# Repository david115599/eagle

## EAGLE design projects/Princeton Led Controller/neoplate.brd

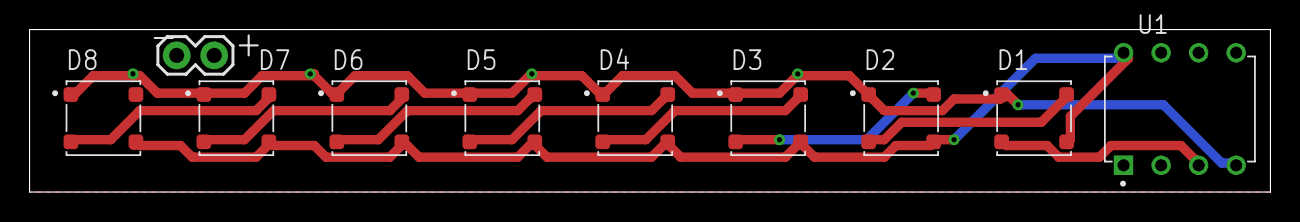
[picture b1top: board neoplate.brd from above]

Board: 2 copper layers, 84.0 x 11.0 mm, 10 parts (0 on the bottom side), 10 nets.

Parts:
D1, D2, D3, D4, D5, D6, D7, D8: 1655; SMD_RGB
JP1: 1X02
U1: ATTINY85-20PU; PDIP-8

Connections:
GND: D1.1, D2.1, D3.1, D4.1, D5.1, D6.1, D7.1, D8.1, JP1.2, U1.4
unnamed: D1.4, D2.2
unnamed: D2.4, D3.2
unnamed: D3.4, D4.2
unnamed: D4.4, D5.2
unnamed: D5.4, D6.2
unnamed: D6.4, D7.2
unnamed: D7.4, D8.2
NEOIN: D1.2, U1.3
VCC: D1.3, D2.3, D3.3, D4.3, D5.3, D6.3, D7.3, D8.3, JP1.1, U1.8

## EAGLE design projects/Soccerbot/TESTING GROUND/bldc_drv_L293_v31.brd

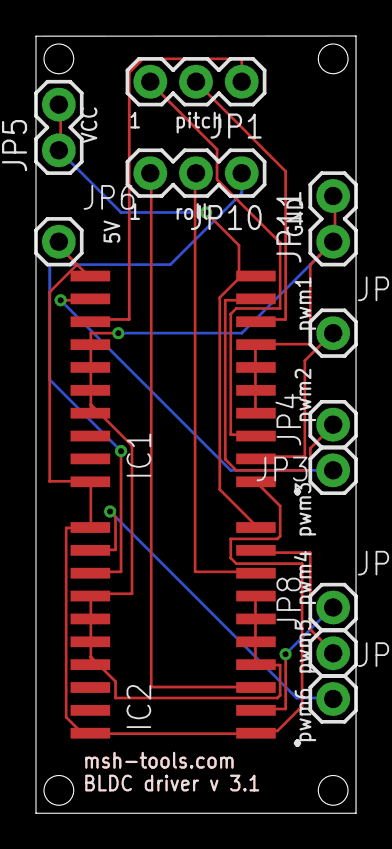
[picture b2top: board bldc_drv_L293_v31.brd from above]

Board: 2 copper layers, 17.8 x 43.2 mm, 13 parts (0 on the bottom side), 15 nets.

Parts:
IC1, IC2: L293DD; SO20
JP1, JP10: 1X03
JP2, JP3, JP4, JP6, JP7, JP8, JP9: M01PTH; 1X01
JP5, JP11: 1X02

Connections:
5V: IC1.1, IC1.11, IC1.20, IC2.1, IC2.11, IC2.20, JP6.1
GND: IC1.4, IC1.5, IC1.6, IC1.7, IC1.14, IC1.15, IC1.16, IC1.17, IC2.4, IC2.5, IC2.6, IC2.7, IC2.14, IC2.15, IC2.16, IC2.17, JP11.1, JP11.2
unnamed: IC2.3, JP10.3
unnamed: IC1.3, JP1.3
unnamed: IC1.8, JP1.2
unnamed: IC1.13, JP1.1
unnamed: IC2.8, JP10.2
unnamed: IC2.13, JP10.1
PWM1: IC1.2, JP2.1
PWM2: IC1.9, JP3.1
PWM3: IC1.12, JP4.1
PWM4: IC2.2, JP7.1
PWM5: IC2.9, JP8.1
PWM6: IC2.12, JP9.1
VCC: IC1.10, IC2.10, JP5.1, JP5.2

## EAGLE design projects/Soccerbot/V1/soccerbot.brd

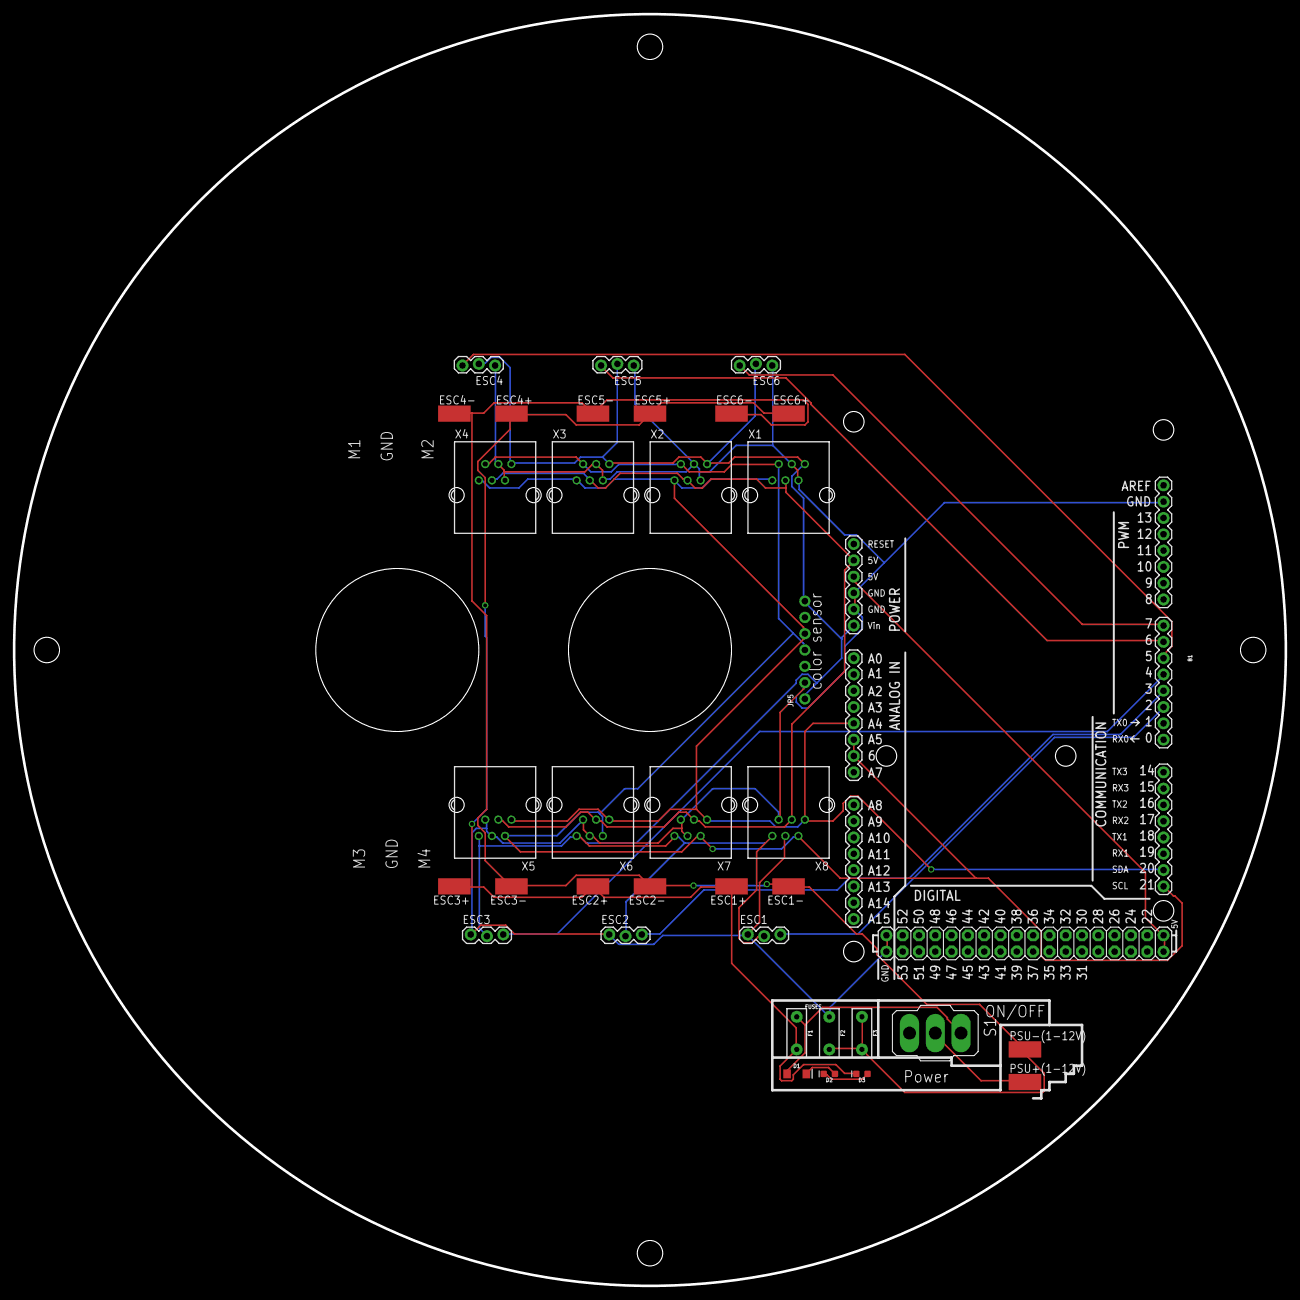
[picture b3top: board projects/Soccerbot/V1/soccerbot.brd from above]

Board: 2 copper layers, 198.1 x 198.1 mm, 37 parts (0 on the bottom side), 18 nets.

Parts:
B1: ARDUINO_MEGA_R3FULL; ARDUINO_MEGA
D1: BLUE; LED-1206
D2: GREEN; LED-0603
D3: RED; LED-0603
ESC1, ESC2, ESC3, ESC4, ESC5, ESC6: 1X03_LOCK
ESC1+, ESC1-, ESC2+, ESC2-, ESC3+, ESC3-, ESC4+, ESC4-, ESC5+, ESC5-, ESC6+, ESC6-: SMD2,54-5,08
F1, F2, F3: 72V/0.25A; PTH
JP5: 1X07_ROUND_70
PSU+(1-12V): SMD2,54-5,08
PSU-(1-12V): SMD2,54-5,08
S1: 320-916
X1, X2, X3, X4, X5, X6, X7, X8: NXT-SOCKET

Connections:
3.3V: B1.3.3V, X1.4, X2.4, X3.4, X4.4, X5.4, X6.4, X7.4, X8.4
5.5V: B1.5V@0, B1.5V@1, B1.5V@2
BAT+: D3.C, ESC1+.1, ESC2+.1, ESC3+.1, ESC4+.1, ESC5+.1, ESC6+.1, F1.P$2
BAT-: ESC1-.1, ESC2-.1, ESC3-.1, ESC4-.1, ESC5-.1, ESC6-.1, F2.P$2, F3.P$1, F3.P$2, PSU-(1-12V).1
D2: B1.2, ESC1.3
D3: B1.3, ESC2.3
D4: B1.4, ESC3.3
D5: B1.5, ESC4.3
D6: B1.6, ESC5.3
D7: B1.7, ESC6.3
GND: B1.GND@0, B1.GND@1, B1.GND@2, B1.GND@3, B1.GND@4, ESC1.1, ESC2.1, ESC3.1, ESC4.1, ESC5.1, ESC6.1, F2.P$1, JP5.2, X1.2, X1.3, X2.2, X2.3, X3.2, X3.3, X4.2, X4.3, X5.2, X5.3, X6.2, X6.3, X7.2, X7.3, X8.2, X8.3
unnamed: D1.C, D2.A
unnamed: PSU+(1-12V).1, S1.2
unnamed: D2.C, D3.A
unnamed: D1.A, F1.P$1, S1.1
SCL: B1.21, B1.A5, JP5.4, X1.5, X2.5, X3.5, X4.5, X5.5, X6.5, X7.5, X8.5
SDA: B1.20, B1.A4, JP5.5, X1.6, X2.6, X3.6, X4.6, X5.6, X6.6, X7.6, X8.6
VIN: B1.VIN, ESC1.2, ESC2.2, ESC3.2, ESC4.2, ESC5.2, ESC6.2, JP5.1, JP5.7, X1.1, X2.1, X3.1, X4.1, X5.1, X6.1, X7.1, X8.1

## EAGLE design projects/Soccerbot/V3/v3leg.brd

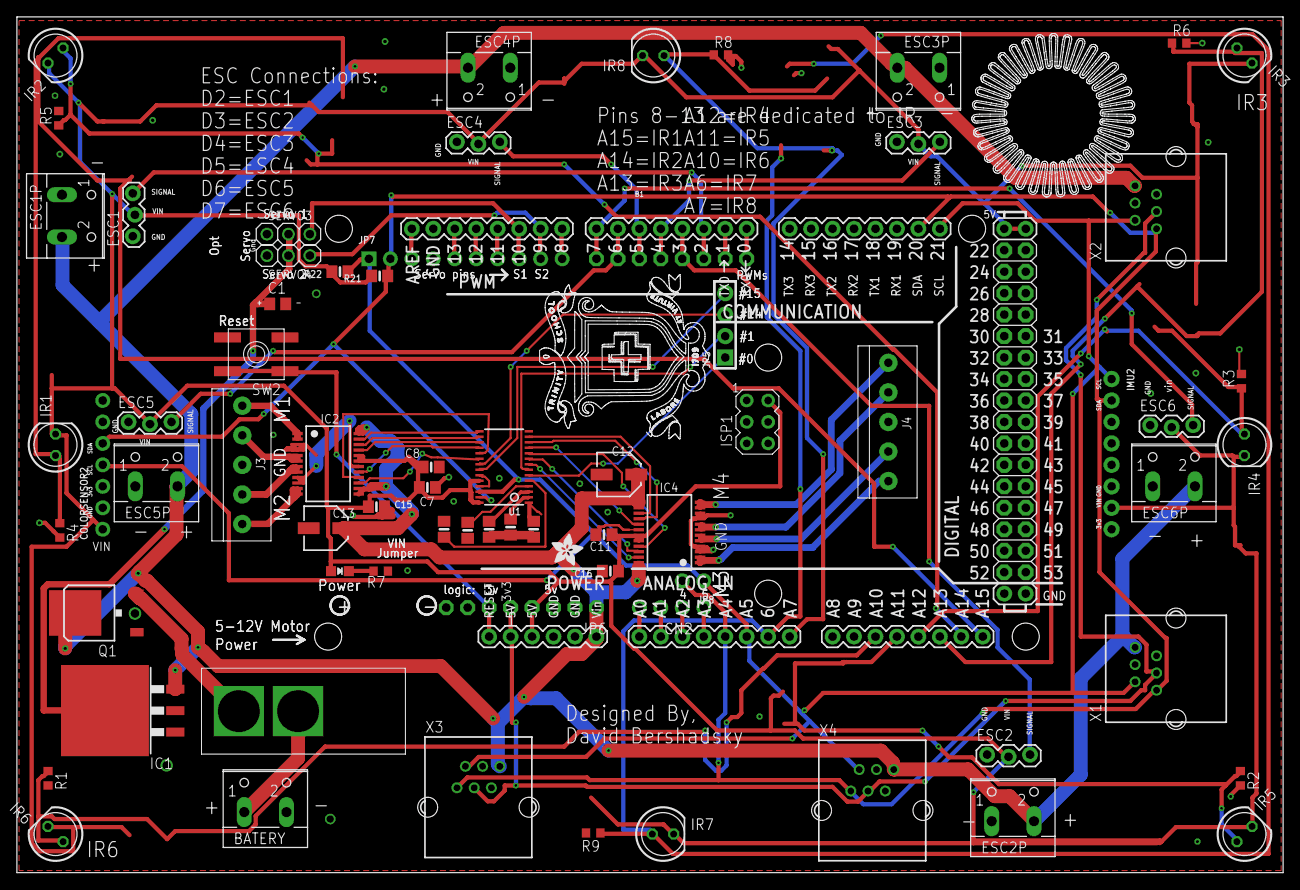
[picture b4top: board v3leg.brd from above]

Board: 2 copper layers, 149.8 x 101.3 mm, 73 parts (1 on the bottom side), 67 nets.

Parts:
B1: ARDUINO_MEGA_R3FULL; ARDUINO_MEGA
BATERY: W237-102
C1: C0805
C7, C8, C11: 0.1uF; 0805-NO
C12: 47uF/16v; PANASONIC_C
C13: 47uF+/16v; PANASONIC_C
C15, C16: 10uF; 0805-NO
CN2: 1X4-CLEANBIG; 1X04-CLEANBIG
COLORSENSOR2: 1X07_ROUND_70
D0-1: 1X08-CLEANBIG
ESC1, ESC2, ESC3, ESC4, ESC5, ESC6: 1X03_LOCK
ESC1P, ESC2P, ESC3P, ESC4P, ESC5P, ESC6P: W237-102
IC1: LM340S-05; TO263-3
IC2, IC4: TB6612FNG; SSOP24
IMU2: 1X08_ROUND_76
IR1, IR2, IR3, IR4, IR5, IR6, IR7, IR8: LED5MM
ISP1: AVRISP-6; AVRISP
J3, J4: 1X5; 1X05-3.5MM
JP5: 1X04_ROUND_76
JP6: 1X08-CLEANBIG
JP7: 1X10_ROUND70
JP8: 1X02_ROUND
LED2: Green; CHIPLED_0805_NOOUTLINE
Q1: AOD417; D-PAK_TO252AA
R1, R2, R3, R4, R5, R6, R8, R9: 49.9k; R0603
R7: 150ohm; R0603
R15, R16, R17, R19, R20: 10k; 0805-NO
R21, R22: 10K; 0805-NO
SERVO3, SERVO4: 1X03
SW2: SPST_TACT-EVQQ2; EVQ-Q2
U1: PCA9685; TSSOP28
U$2: TOGGLESWITCH
U$17: ADAFRUIT_TEXT_30MM
U$18: ADAFRUIT_3.5MM
X1, X2, X3, X4: NXT-SOCKET

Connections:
3.3V: B1.3.3V, JP6.5, X1.4, X2.4, X3.4, X4.4
5.5V: B1.5V@0, B1.5V@1, B1.5V@2, C7.1, C8.1, C11.1, C15.1, C16.1, COLORSENSOR2.1, ESC1.2, ESC2.2, ESC3.2, ESC4.2, ESC5.2, ESC6.2, IC2.19, IC2.20, IC4.19, IC4.20, IMU2.7, IR1.K, IR2.K, IR3.K, IR4.K, IR5.K, IR6.K, IR7.K, IR8.K, ISP1.2, JP6.4, LED2.A, R21.2, R22.2, U1.24, U1.28
A0: R15.2, U1.1
A0A: B1.A0, CN2.4
A1: R16.2, U1.2
A1A: B1.A1, CN2.3
A2: R17.2, U1.3
A2A: B1.A2, CN2.2
A3: R19.2, U1.4
A3A: B1.A3, CN2.1
A4: R20.2, U1.5
A6: B1.A6, IR7.A, R9.1
A7: B1.A7, IR8.A, R8.1
A10: B1.A10, IR6.A, R1.1
A11: B1.A11, IR5.A, R2.1
A12: B1.A12, IR4.A, R3.1
A13: B1.A13, IR3.A, R6.1
A14: B1.A14, IR2.A, R5.1
A15: B1.A15, IR1.A, R4.1
AREF: B1.AREF, JP7.3
BAT+: B1.VIN, C12.+, C13.+, ESC1P.2, ESC2P.2, ESC3P.2, ESC4P.2, ESC5P.2, ESC6P.2, IC1.3, IC2.13, IC2.14, IC2.24, IC4.13, IC4.14, IC4.24, JP6.1, Q1.4, X1.1, X2.1, X3.1, X4.1
D0: B1.0, D0-1.1
D1: B1.1, D0-1.2
D2: B1.2, D0-1.3, ESC1.3
D3: B1.3, D0-1.4, ESC2.3
D4: B1.4, D0-1.5, ESC3.3
D5: B1.5, D0-1.6, ESC4.3
D6: B1.6, D0-1.7, ESC5.3
D7: B1.7, D0-1.8, ESC6.3
D8: B1.8, JP7.10
D9: B1.9, JP7.9, SERVO4.3
D10: B1.10, JP7.8, SERVO3.3
D11: B1.11, JP7.7
D12: B1.12, JP7.6
D13: B1.13, JP7.5
GND: B1.GND@0, B1.GND@1, B1.GND@2, B1.GND@3, B1.GND@4, BATERY.2, C1.2, C7.2, C8.2, C11.2, C12.-, C13.-, C15.2, C16.2, COLORSENSOR2.2, ESC1.1, ESC1P.1, ESC2.1, ESC2P.1, ESC3.1, ESC3P.1, ESC4.1, ESC4P.1, ESC5.1, ESC5P.1, ESC6.1, ESC6P.1, IC1.1, IC2.3, IC2.4, IC2.9, IC2.10, IC2.18, IC4.3, IC4.4, IC4.9, IC4.10, IC4.18, IMU2.6, ISP1.6, J3.3, J4.3, JP6.2, JP6.3, JP7.4, Q1.1, R1.2, R2.2, R3.2, R4.2, R5.2, R6.2, R7.1, R8.2, R9.2, R15.1, R16.1, R17.1, R19.1, R20.1, SERVO3.1, SERVO4.1, SW2.A, SW2.A', U1.14, U1.23, U1.25, X1.2, X1.3, X2.2, X2.3, X3.2, X3.3, X4.2, X4.3
M1A1: IC2.1, IC2.2, J3.5
M1B1: IC2.5, IC2.6, J3.4
M2A1: IC2.11, IC2.12, J3.1
M2B1: IC2.7, IC2.8, J3.2
M3A1: IC4.1, IC4.2, J4.1
M3B1: IC4.5, IC4.6, J4.2
M4A1: IC4.11, IC4.12, J4.5
M4B1: IC4.7, IC4.8, J4.4
unnamed: LED2.C, R7.2
unnamed: BATERY.1, U$2.IN
unnamed: Q1.3, U$2.OUT
PWM0: JP5.1, U1.6
PWM1: JP5.2, U1.7
PWM2: IC4.23, U1.8
PWM3: IC4.22, U1.9
PWM4: IC4.21, U1.10
PWM5: IC4.17, U1.11
PWM6: IC4.16, U1.12
PWM7: IC4.15, U1.13
PWM8: IC2.23, U1.15
PWM9: IC2.22, U1.16
PWM10: IC2.21, U1.17
PWM11: IC2.17, U1.18
PWM12: IC2.16, U1.19
PWM13: IC2.15, U1.20
PWM14: JP5.3, U1.21
PWM15: JP5.4, U1.22
RESET: B1.RESET, JP6.6, SW2.B, SW2.B'
SCL: B1.21, B1.A5, COLORSENSOR2.4, IMU2.1, JP7.1, JP8.1, R22.1, U1.26, X1.5, X2.5, X3.5, X4.5
SDA: B1.20, B1.A4, COLORSENSOR2.5, IMU2.2, JP7.2, JP8.2, R21.1, U1.27, X1.6, X2.6, X3.6, X4.6
SERVO5V: C1.1, IC1.TAB, SERVO3.2, SERVO4.2

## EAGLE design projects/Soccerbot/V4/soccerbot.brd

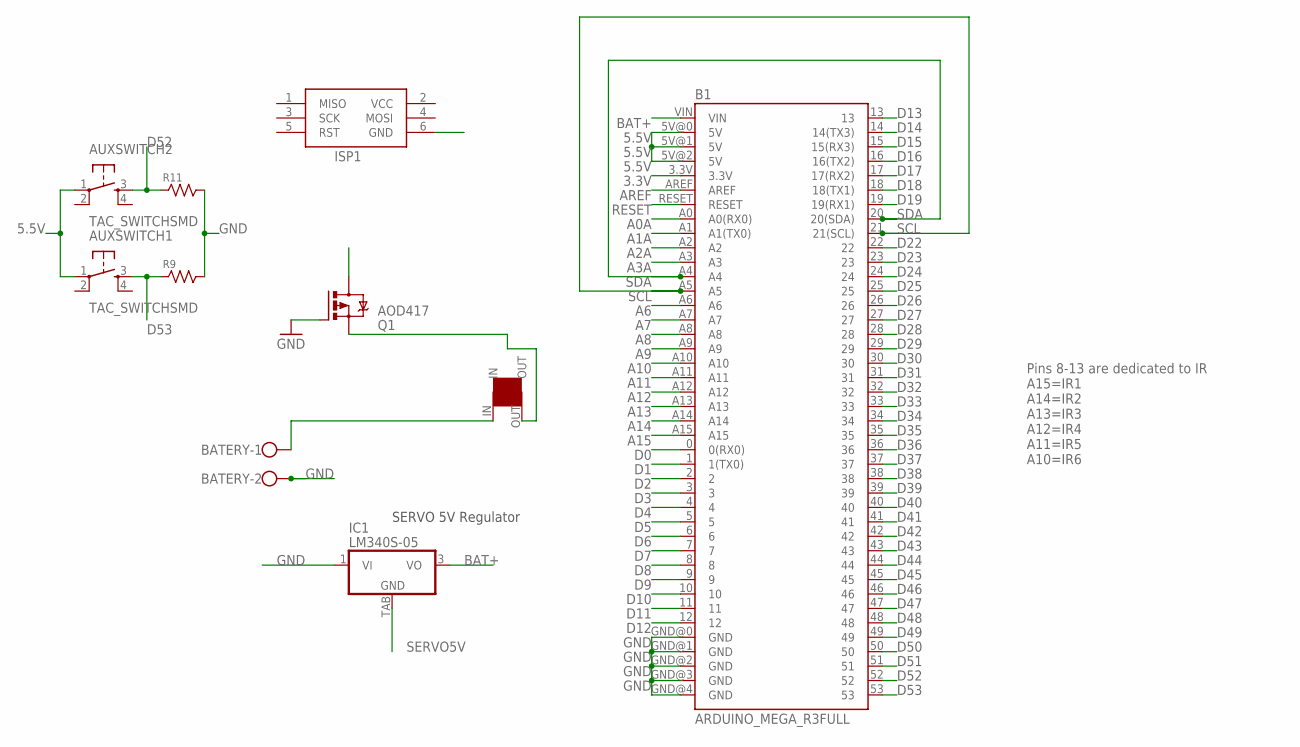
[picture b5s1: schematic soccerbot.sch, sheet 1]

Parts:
AUXSWITCH1, AUXSWITCH2: TAC_SWITCHSMD; TACTILE-SWITCH-SMD
B1: ARDUINO_MEGA_R3FULL; ARDUINO_MEGA
BATERY: W237-102; MPN MA522-500M02
IC1: LM340S-05; TO263-3; MPN LM1085ISX-5.0/NOPB
ISP1: AVRISP-6; AVRISP
Q1: AOD417; D-PAK_TO252AA; MPN AUIRFR540ZTRL
R9, R11: RESISTOR-0603; 0603
U$2: TOGGLESWITCH

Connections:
3.3V: B1.3.3V; also elsewhere on the board
5.5V: AUXSWITCH1.1, AUXSWITCH2.1, B1.5V@0 (5V), B1.5V@1 (5V), B1.5V@2 (5V), ISP1.2 (VCC); also elsewhere on the board
A0A: B1.A0 (A0(RX0))
A1A: B1.A1 (A1(TX0))
A2A: B1.A2
A3A: B1.A3
A6: B1.A6; also elsewhere on the board
A7: B1.A7
A8: B1.A8; also elsewhere on the board
A9: B1.A9
A10: B1.A10; also elsewhere on the board
A11: B1.A11; also elsewhere on the board
A12: B1.A12; also elsewhere on the board
A13: B1.A13; also elsewhere on the board
A14: B1.A14; also elsewhere on the board
A15: B1.A15; also elsewhere on the board
AREF: B1.AREF
BAT+: B1.VIN, IC1.3 (VO), Q1.4 (D); also elsewhere on the board
D0: B1.0 (0(RX0))
D1: B1.1 (1(TX0))
D2: B1.2; also elsewhere on the board
D3: B1.3; also elsewhere on the board
D4: B1.4; also elsewhere on the board
D5: B1.5; also elsewhere on the board
D6: B1.6; also elsewhere on the board
D7: B1.7; also elsewhere on the board
D8: B1.8
D9: B1.9
D10: B1.10
D11: B1.11
D12: B1.12
D13: B1.13
D14: B1.14 (14(TX3))
D15: B1.15 (15(RX3))
D16: B1.16 (16(TX2))
D17: B1.17 (17(RX2))
D18: B1.18 (18(TX1))
D19: B1.19 (19(RX1))
D22: B1.22
D23: B1.23
D24: B1.24
D25: B1.25
D26: B1.26
D27: B1.27
D28: B1.28
D29: B1.29
D30: B1.30
D31: B1.31
D32: B1.32
D33: B1.33
D34: B1.34
D35: B1.35
D36: B1.36
D37: B1.37
D38: B1.38
D39: B1.39
D40: B1.40
D41: B1.41
D42: B1.42
D43: B1.43
D44: B1.44
D45: B1.45
D46: B1.46
D47: B1.47
D48: B1.48
D49: B1.49
D50: B1.50
D51: B1.51
D52: AUXSWITCH2.3, B1.52, R11.1
D53: AUXSWITCH1.3, B1.53, R9.1
GND: B1.GND@0 (GND), B1.GND@1 (GND), B1.GND@2 (GND), B1.GND@3 (GND), B1.GND@4 (GND), BATERY.2, IC1.1 (VI), ISP1.6 (GND), Q1.1 (G), R9.2, R11.2; also elsewhere on the board
unnamed: BATERY.1, U$2.IN
unnamed: Q1.3 (S), U$2.OUT
RESET: B1.RESET
SCL: B1.21 (21(SCL)), B1.A5; also elsewhere on the board
SDA: B1.20 (20(SDA)), B1.A4; also elsewhere on the board
SERVO5V: IC1.TAB (GND)

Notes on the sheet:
Pins 8-13 are dedicated to IR A15=IR1 A14=IR2 A13=IR3 A12=IR4 A11=IR5 A10=IR6
SERVO 5V Regulator

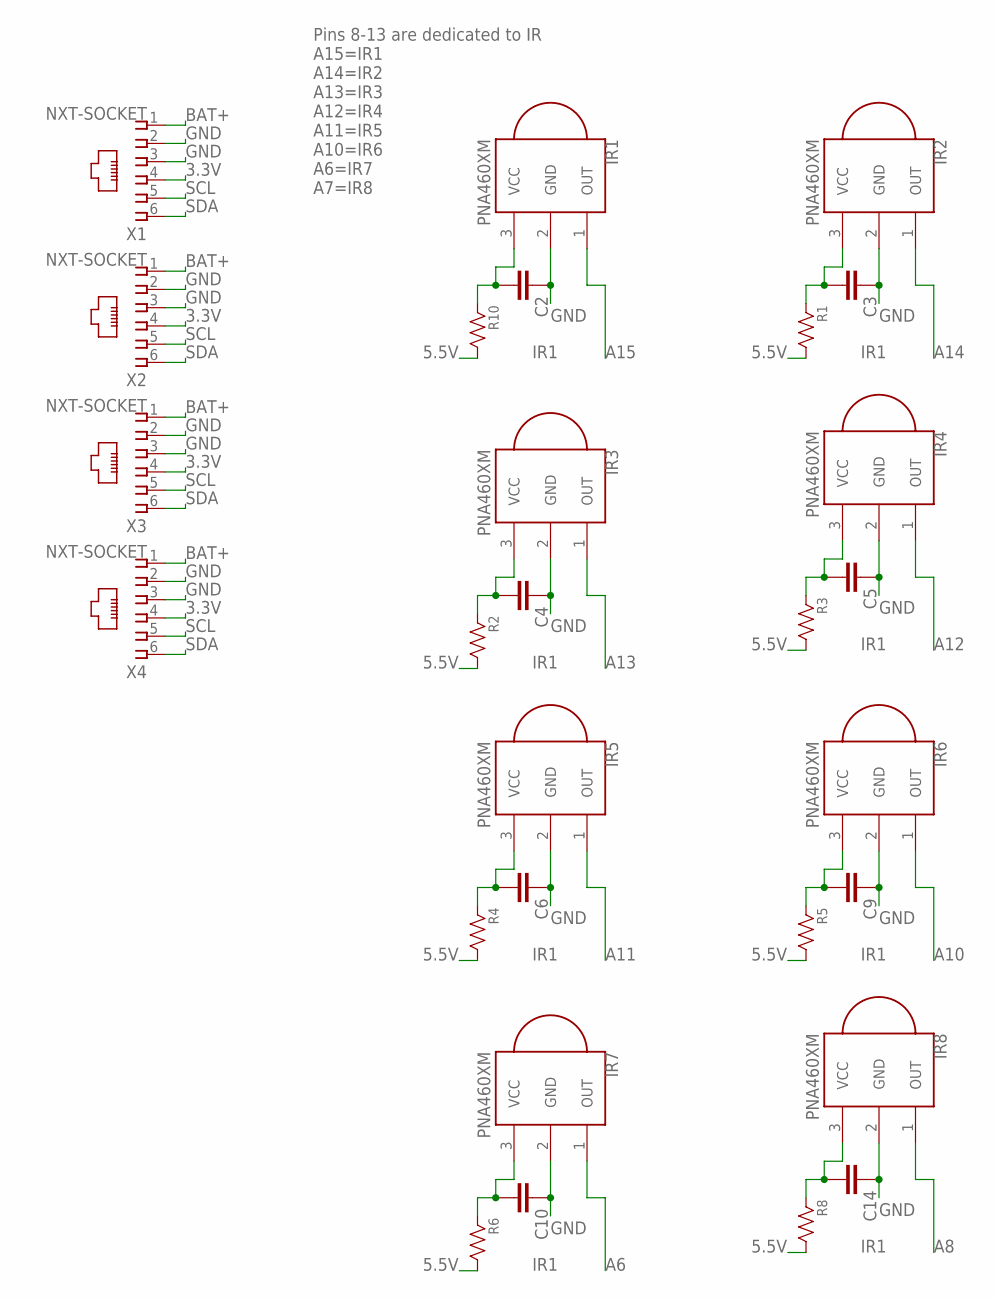
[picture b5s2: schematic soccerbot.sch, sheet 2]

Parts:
C2, C3, C4, C5, C6, C9, C10, C14: CAPACITOR; C0603
IR1, IR2, IR3, IR4, IR5, IR6, IR7, IR8: PNA460XM
R1, R2, R3, R4, R5, R6, R8, R10: RESISTOR-0603-NARROW; 0603-NARROW
X1, X2, X3, X4: NXT-SOCKET; MPN RJE01-660-01

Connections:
3.3V: X1.4, X2.4, X3.4, X4.4; also elsewhere on the board
5.5V: R1.2, R2.2, R3.2, R4.2, R5.2, R6.2, R8.2, R10.2; also elsewhere on the board
A6: IR7.1 (OUT); also elsewhere on the board
A8: IR8.1 (OUT); also elsewhere on the board
A10: IR6.1 (OUT); also elsewhere on the board
A11: IR5.1 (OUT); also elsewhere on the board
A12: IR4.1 (OUT); also elsewhere on the board
A13: IR3.1 (OUT); also elsewhere on the board
A14: IR2.1 (OUT); also elsewhere on the board
A15: IR1.1 (OUT); also elsewhere on the board
BAT+: X1.1, X2.1, X3.1, X4.1; also elsewhere on the board
GND: C2.1, C3.1, C4.1, C5.1, C6.1, C9.1, C10.1, C14.1, IR1.2 (GND), IR2.2 (GND), IR3.2 (GND), IR4.2 (GND), IR5.2 (GND), IR6.2 (GND), IR7.2 (GND), IR8.2 (GND), X1.2, X1.3, X2.2, X2.3, X3.2, X3.3, X4.2, X4.3; also elsewhere on the board
unnamed: C3.2, IR2.3 (VCC), R1.1
unnamed: C2.2, IR1.3 (VCC), R10.1
unnamed: C4.2, IR3.3 (VCC), R2.1
unnamed: C5.2, IR4.3 (VCC), R3.1
unnamed: C6.2, IR5.3 (VCC), R4.1
unnamed: C9.2, IR6.3 (VCC), R5.1
unnamed: C10.2, IR7.3 (VCC), R6.1
unnamed: C14.2, IR8.3 (VCC), R8.1
SCL: X1.5, X2.5, X3.5, X4.5; also elsewhere on the board
SDA: X1.6, X2.6, X3.6, X4.6; also elsewhere on the board

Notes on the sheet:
Pins 8-13 are dedicated to IR A15=IR1 A14=IR2 A13=IR3 A12=IR4 A11=IR5 A10=IR6 A6=IR7 A7=IR8
IR1

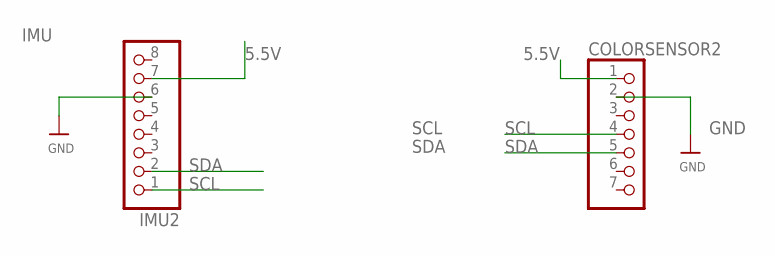
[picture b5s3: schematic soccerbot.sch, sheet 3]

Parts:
COLORSENSOR2: HEADER-1X770MIL; 1X07_ROUND_70
IMU2: HEADER-1X876MIL; 1X08_ROUND_76

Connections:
5.5V: COLORSENSOR2.1, IMU2.7; also elsewhere on the board
GND: COLORSENSOR2.2, IMU2.6; also elsewhere on the board
SCL: COLORSENSOR2.4, IMU2.1; also elsewhere on the board
SDA: COLORSENSOR2.5, IMU2.2; also elsewhere on the board

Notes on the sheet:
IMU

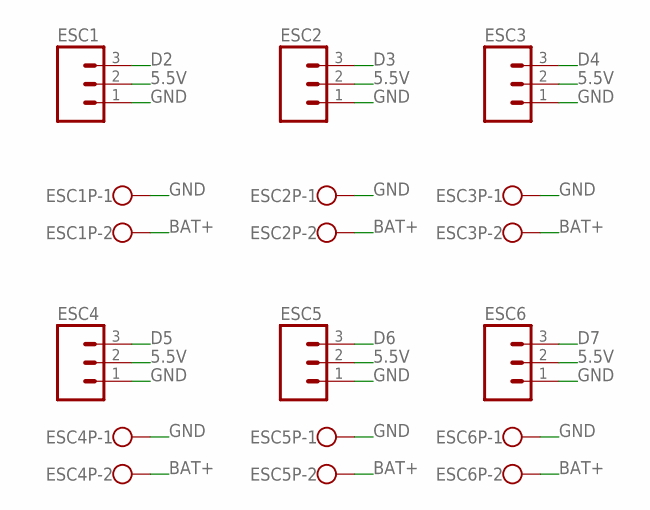
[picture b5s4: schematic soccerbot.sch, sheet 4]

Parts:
ESC1, ESC2, ESC3, ESC4, ESC5, ESC6: M03LOCK; 1X03_LOCK; MPN 22-11-2032
ESC1P, ESC2P, ESC3P, ESC4P, ESC5P, ESC6P: W237-102; MPN MA522-500M02

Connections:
5.5V: ESC1.2, ESC2.2, ESC3.2, ESC4.2, ESC5.2, ESC6.2; also elsewhere on the board
BAT+: ESC1P.2, ESC2P.2, ESC3P.2, ESC4P.2, ESC5P.2, ESC6P.2; also elsewhere on the board
D2: ESC1.3; also elsewhere on the board
D3: ESC2.3; also elsewhere on the board
D4: ESC3.3; also elsewhere on the board
D5: ESC4.3; also elsewhere on the board
D6: ESC5.3; also elsewhere on the board
D7: ESC6.3; also elsewhere on the board
GND: ESC1.1, ESC1P.1, ESC2.1, ESC2P.1, ESC3.1, ESC3P.1, ESC4.1, ESC4P.1, ESC5.1, ESC5P.1, ESC6.1, ESC6P.1; also elsewhere on the board

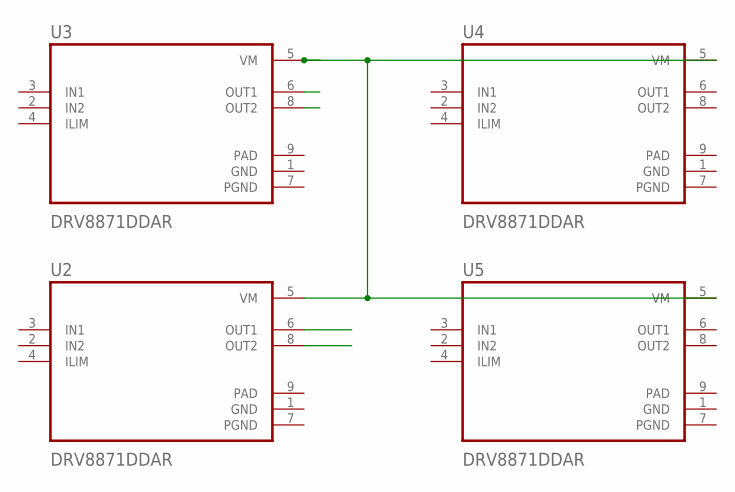
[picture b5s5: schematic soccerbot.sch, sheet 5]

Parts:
U2, U3, U4, U5: DRV8871DDAR; SOIC127P600X170-8N

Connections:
GND: U2.1 (GND), U3.1 (GND), U4.1 (GND), U5.1 (GND); also elsewhere on the board
unnamed: U2.5 (VM), U3.5 (VM), U4.5 (VM), U5.5 (VM)
PAD: U2.9 (PAD), U3.9 (PAD), U4.9 (PAD), U5.9 (PAD)
PGND: U2.7 (PGND), U3.7 (PGND), U4.7 (PGND), U5.7 (PGND)

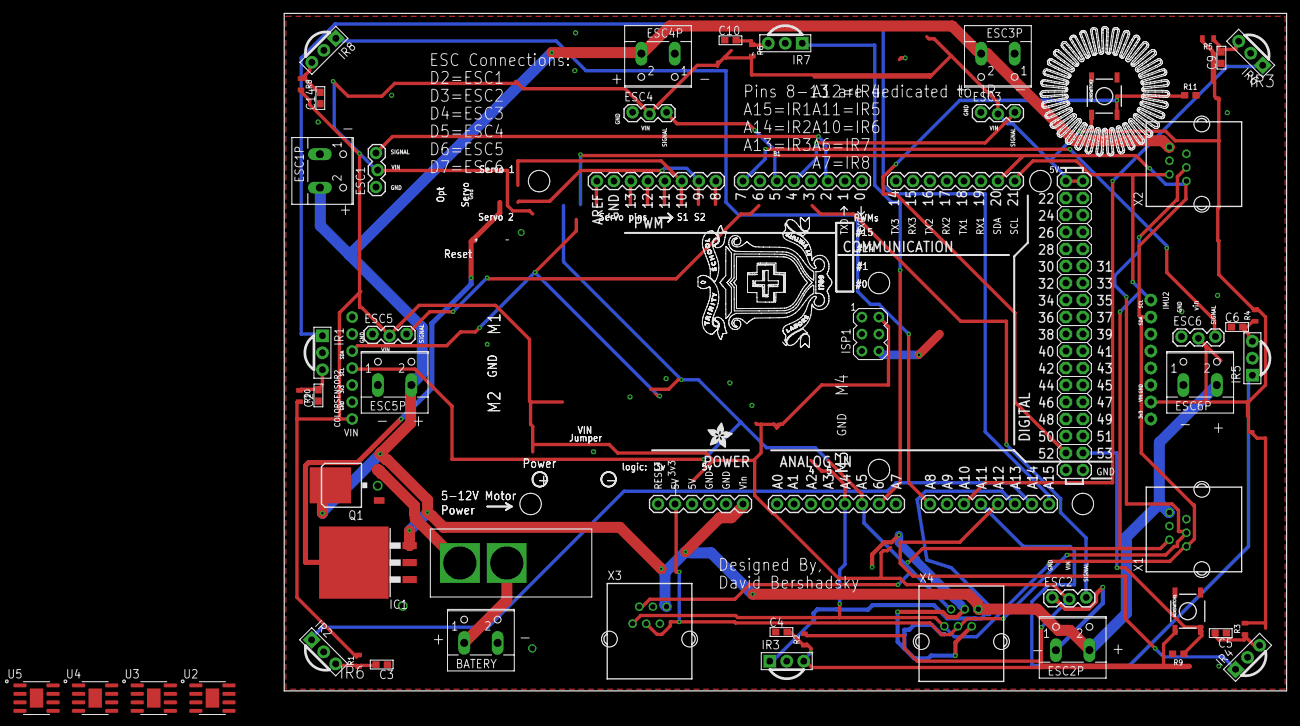
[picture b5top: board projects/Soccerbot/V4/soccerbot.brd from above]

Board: 2 copper layers, 149.8 x 101.3 mm, 58 parts (1 on the bottom side), 35 nets.

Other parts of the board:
U$17: ADAFRUIT_TEXT_30MM
U$18: ADAFRUIT_3.5MM

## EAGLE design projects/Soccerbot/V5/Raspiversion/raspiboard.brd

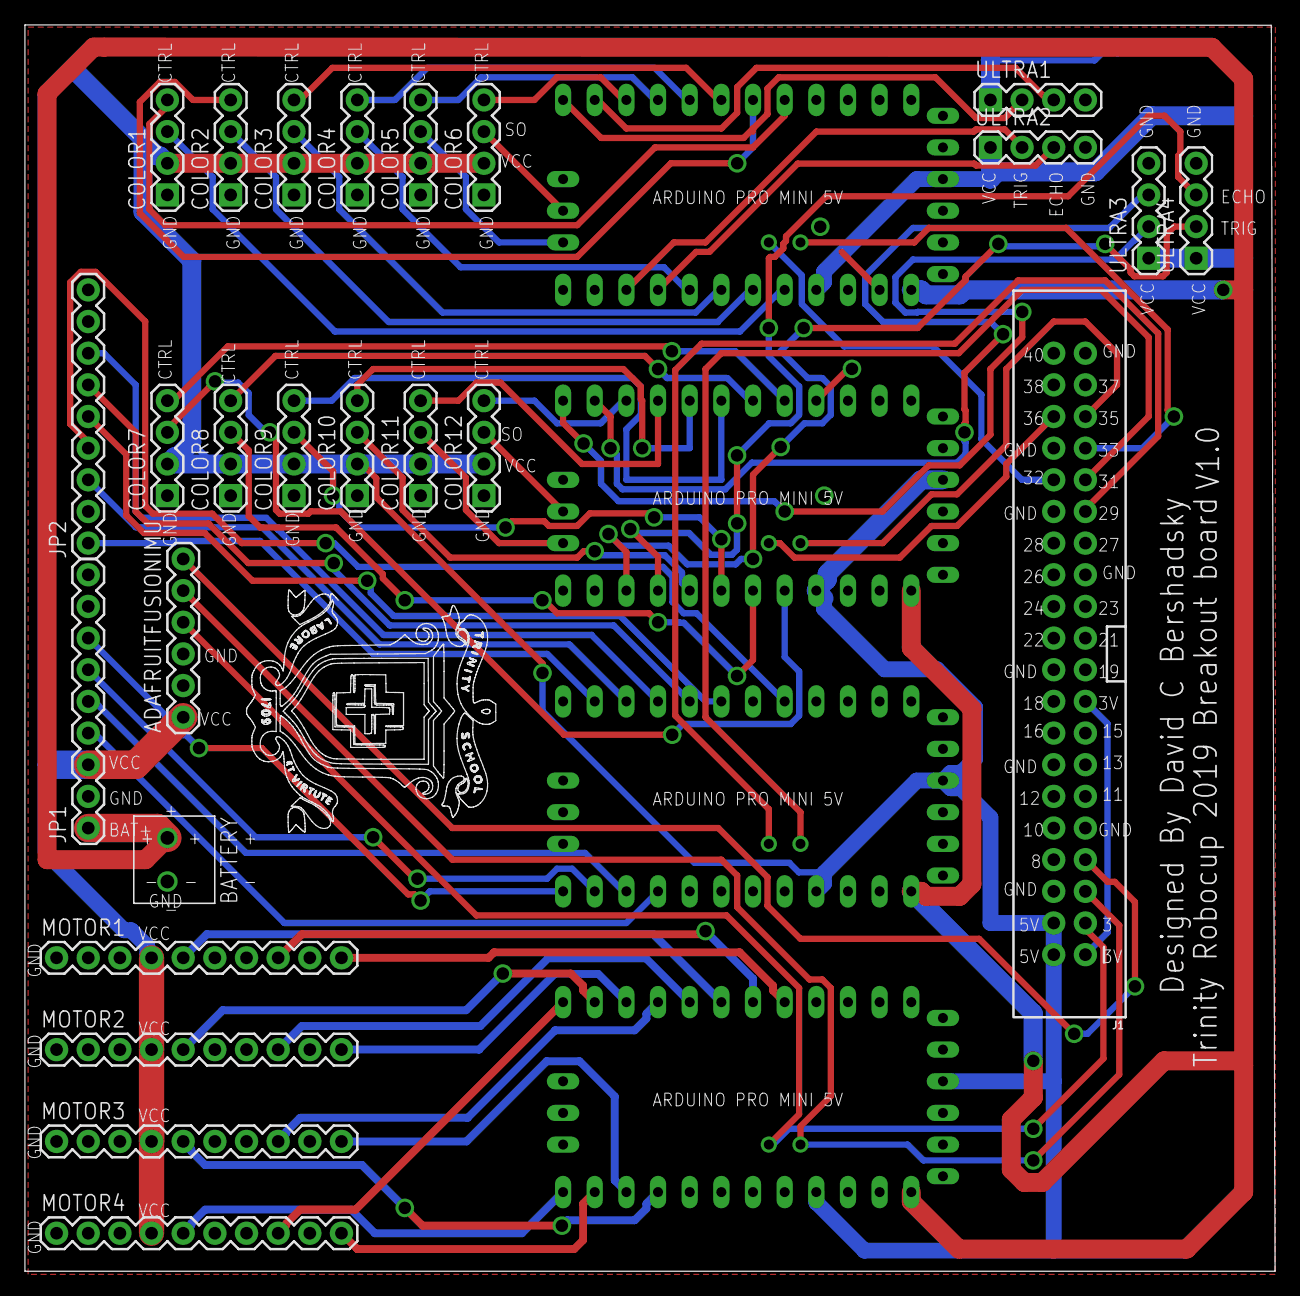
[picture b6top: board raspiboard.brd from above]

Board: 2 copper layers, 100.3 x 100.0 mm, 29 parts (0 on the bottom side), 67 nets.

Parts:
ADAFRUITFUSIONIMU: 1X06
BATTERY: ED555/2DS
COLOR1, COLOR2, COLOR3, COLOR4, COLOR5, COLOR6, COLOR7, COLOR8, COLOR9, COLOR10, COLOR11, COLOR12: 1X04
J1: RASPBERRYPI-40-PIN-GPIO_PTH; 2X20_SHROUDED
JP1, JP2: M09; 1X09
MOTOR1, MOTOR2, MOTOR3, MOTOR4: M10"; 1X10
U$1, U$3, U$4, U$5: ABK-PRO-MINI
ULTRA1, ULTRA2, ULTRA3, ULTRA4: 1X04

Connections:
3.3V: J1.1, J1.17
BAT+: BATTERY.1, JP1.1, U$1.RAW, U$3.RAW, U$4.RAW, U$5.RAW
CTRL1: COLOR1.4, U$3.D2
CTRL2: COLOR2.4, U$3.D3
CTRL3: COLOR3.4, U$3.D4
CTRL4: COLOR4.4, U$3.D5
CTRL5: COLOR5.4, U$3.D6
CTRL6: COLOR6.4, U$3.D7
CTRL7: COLOR7.4, U$5.D2
CTRL8: COLOR8.4, U$5.D3
CTRL9: COLOR9.4, U$5.D4
CTRL10: COLOR10.4, U$5.D5
CTRL11: COLOR11.4, U$5.D6
CTRL12: COLOR12.4, U$5.D7
D7: MOTOR2.10, U$1.D7
D12: MOTOR3.10, U$1.D12
D13: MOTOR3.5, U$1.D13
ECHO1: U$3.D8, ULTRA1.3
ECHO2: U$3.D13, ULTRA2.3
ECHO3: U$5.D8, ULTRA3.3
ECHO4: U$5.D13, ULTRA4.3
EN: JP2.1, U$4.D8
GND: ADAFRUITFUSIONIMU.3, BATTERY.2, COLOR1.1, COLOR2.1, COLOR3.1, COLOR4.1, COLOR5.1, COLOR6.1, COLOR7.1, COLOR8.1, COLOR9.1, COLOR10.1, COLOR11.1, COLOR12.1, J1.6, J1.9, J1.14, J1.20, J1.25, J1.30, J1.34, J1.39, JP1.2, MOTOR1.1, MOTOR1.3, MOTOR2.1, MOTOR2.3, MOTOR3.1, MOTOR3.3, MOTOR4.1, MOTOR4.3, U$1.GND, U$1.GND1, U$1.GND2, U$1.GND3, U$1.GND4, U$3.GND, U$3.GND1, U$3.GND2, U$3.GND3, U$3.GND4, U$4.GND, U$4.GND1, U$4.GND2, U$4.GND3, U$4.GND4, U$5.GND, U$5.GND1, U$5.GND2, U$5.GND3, U$5.GND4, ULTRA1.4, ULTRA2.4, ULTRA3.4, ULTRA4.4
IMURESET: ADAFRUITFUSIONIMU.6, J1.7
INV: JP2.3, U$4.D7
M1IN1: JP1.5, U$4.D12
M1IN2: JP1.4, U$4.D13
M1PWMD1: JP1.7, U$4.D10
M1PWMD2: JP1.6, U$4.D11
M2IN1: JP2.5, U$4.D4
M2IN2: JP2.4, U$4.D2
M2PWMD1: JP2.7, U$4.D6
M2PWMD2: JP2.6, U$4.D5
unnamed: MOTOR1.10, U$1.D2
unnamed: MOTOR1.5, U$1.D4
unnamed: MOTOR2.5, U$1.D8
PWM1: MOTOR1.8, U$1.D3
PWM2: MOTOR2.8, U$1.D5
PWM3: MOTOR3.8, U$1.D6
PWM4: MOTOR4.8, U$1.D9
PWM5: MOTOR4.10, U$1.D11
PWM6: MOTOR4.5, U$1.D10
SCL0: ADAFRUITFUSIONIMU.5, J1.5, U$1.A5
SCL1: J1.31, U$4.A5
SCL2: J1.33, U$3.A5
SCL3: J1.35, U$5.A5
SDA0: ADAFRUITFUSIONIMU.4, J1.3, U$1.A4
SDA1: J1.29, U$4.A4
SDA2: J1.32, U$3.A4
SDA3: J1.36, U$5.A4
SO1: COLOR1.3, U$3.A0
SO2: COLOR2.3, U$3.A1
SO3: COLOR3.3, U$3.A2
SO4: COLOR4.3, U$3.A3
SO5: COLOR5.3, U$3.A7
SO6: COLOR6.3, U$3.A6
SO7: COLOR7.3, U$5.A0
SO8: COLOR8.3, U$5.A1
SO9: COLOR9.3, U$5.A2
SO10: COLOR10.3, U$5.A3
SO11: COLOR11.3, U$5.A7
SO12: COLOR12.3, U$5.A6
TRIG1: U$3.D9, ULTRA1.2
TRIG2: U$3.D12, ULTRA2.2
TRIG3: U$5.D9, ULTRA3.2
TRIG4: U$5.D12, ULTRA4.2
VCC: ADAFRUITFUSIONIMU.1, COLOR1.2, COLOR2.2, COLOR3.2, COLOR4.2, COLOR5.2, COLOR6.2, COLOR7.2, COLOR8.2, COLOR9.2, COLOR10.2, COLOR11.2, COLOR12.2, J1.2, J1.4, JP1.3, MOTOR1.4, MOTOR2.4, MOTOR3.4, MOTOR4.4, U$1.VCC, U$1.VCC1, U$3.VCC, U$3.VCC1, U$4.VCC, U$4.VCC1, U$5.VCC, U$5.VCC1, ULTRA1.1, ULTRA2.1, ULTRA3.1, ULTRA4.1

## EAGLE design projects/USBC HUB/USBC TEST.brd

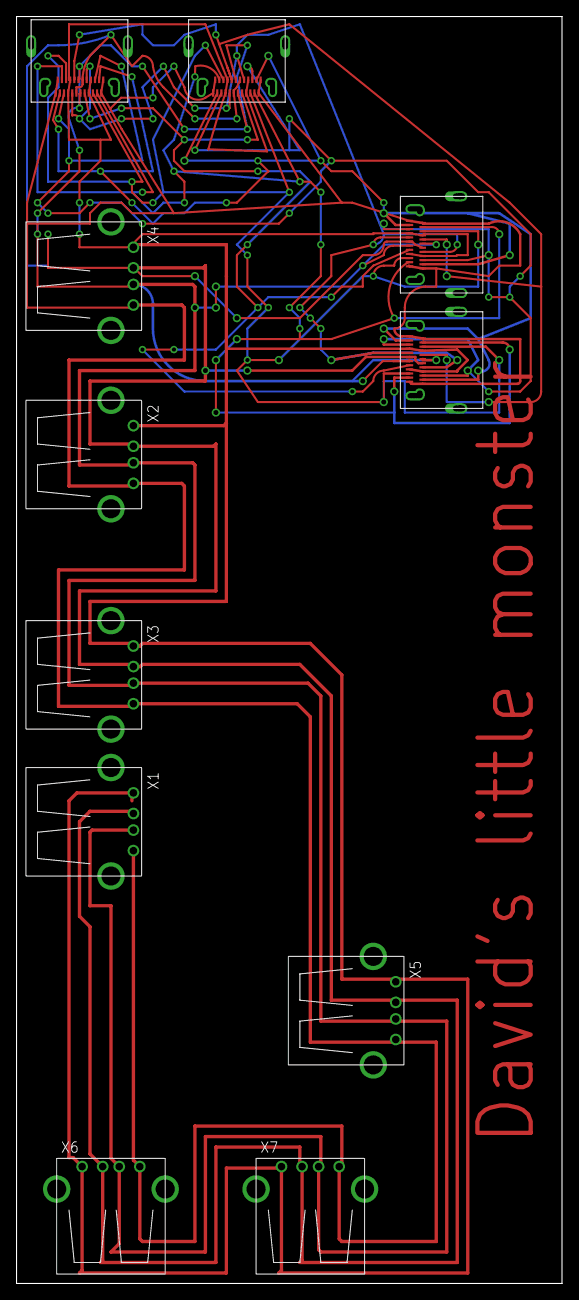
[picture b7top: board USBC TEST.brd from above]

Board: 2 copper layers, 66.0 x 153.3 mm, 11 parts (0 on the bottom side), 11 nets.

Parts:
U$1, U$2, U$3, U$4: USB-TYPE-C; USB-TYPE-C-SMT
X1, X2, X3, X4, X5, X6, X7: USB-A-H

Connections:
CC2/YCONN: U$1.B5, U$2.B5, U$3.B5, U$4.B5
CC/YCONN: U$1.5, U$2.5, U$3.5, U$4.5
D+: U$1.6, U$1.B6, U$2.6, U$2.B6, U$3.6, U$3.B6, U$4.6, U$4.B6, X1.D+, X2.D+, X3.D+, X4.D+, X5.D+, X6.D+, X7.D+
D-: U$1.7, U$1.B7, U$2.7, U$2.B7, U$3.7, U$3.B7, U$4.7, U$4.B7, X1.D-, X2.D-, X3.D-, X4.D-, X5.D-, X6.D-, X7.D-
GND: U$1.1, U$1.12, U$1.B1, U$1.B12, U$2.1, U$2.12, U$2.B1, U$2.B12, U$3.1, U$3.12, U$3.B1, U$3.B12, U$4.1, U$4.12, U$4.B1, U$4.B12, X1.GND, X2.GND, X3.GND, X4.GND, X5.GND, X6.GND, X7.GND
SBU: U$1.8, U$1.B8, U$2.8, U$2.B8, U$3.8, U$3.B8, U$4.8, U$4.B8
SSRX+: U$1.11, U$1.B11, U$2.11, U$2.B11, U$3.11, U$3.B11, U$4.11, U$4.B11
SSRX-: U$1.10, U$1.B10, U$2.10, U$2.B10, U$3.10, U$3.B10, U$4.10, U$4.B10
SSTX+: U$1.2, U$1.B2, U$2.2, U$2.B2, U$3.2, U$3.B2, U$4.2, U$4.B2
SSTX-: U$1.3, U$1.B3, U$2.3, U$2.B3, U$3.3, U$3.B3, U$4.3, U$4.B3
VBUS: U$1.4, U$1.9, U$1.B4, U$1.B9, U$2.4, U$2.9, U$2.B4, U$2.B9, U$3.4, U$3.9, U$3.B4, U$3.B9, U$4.4, U$4.9, U$4.B4, U$4.B9, X1.VBUS, X2.VBUS, X3.VBUS, X4.VBUS, X5.VBUS, X6.VBUS, X7.VBUS

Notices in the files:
parts and their libraries:
SparkFun-Connectors: Licensing: CC v3.0 Share-Alike You are welcome to use this library for commercial purposes.
microbuilder: This work is placed in the public domain, and may be freely used for commercial and non-commercial work with the following conditions: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
